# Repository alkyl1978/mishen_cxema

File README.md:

Схемы и прошивки основного блока и ракеток мишени

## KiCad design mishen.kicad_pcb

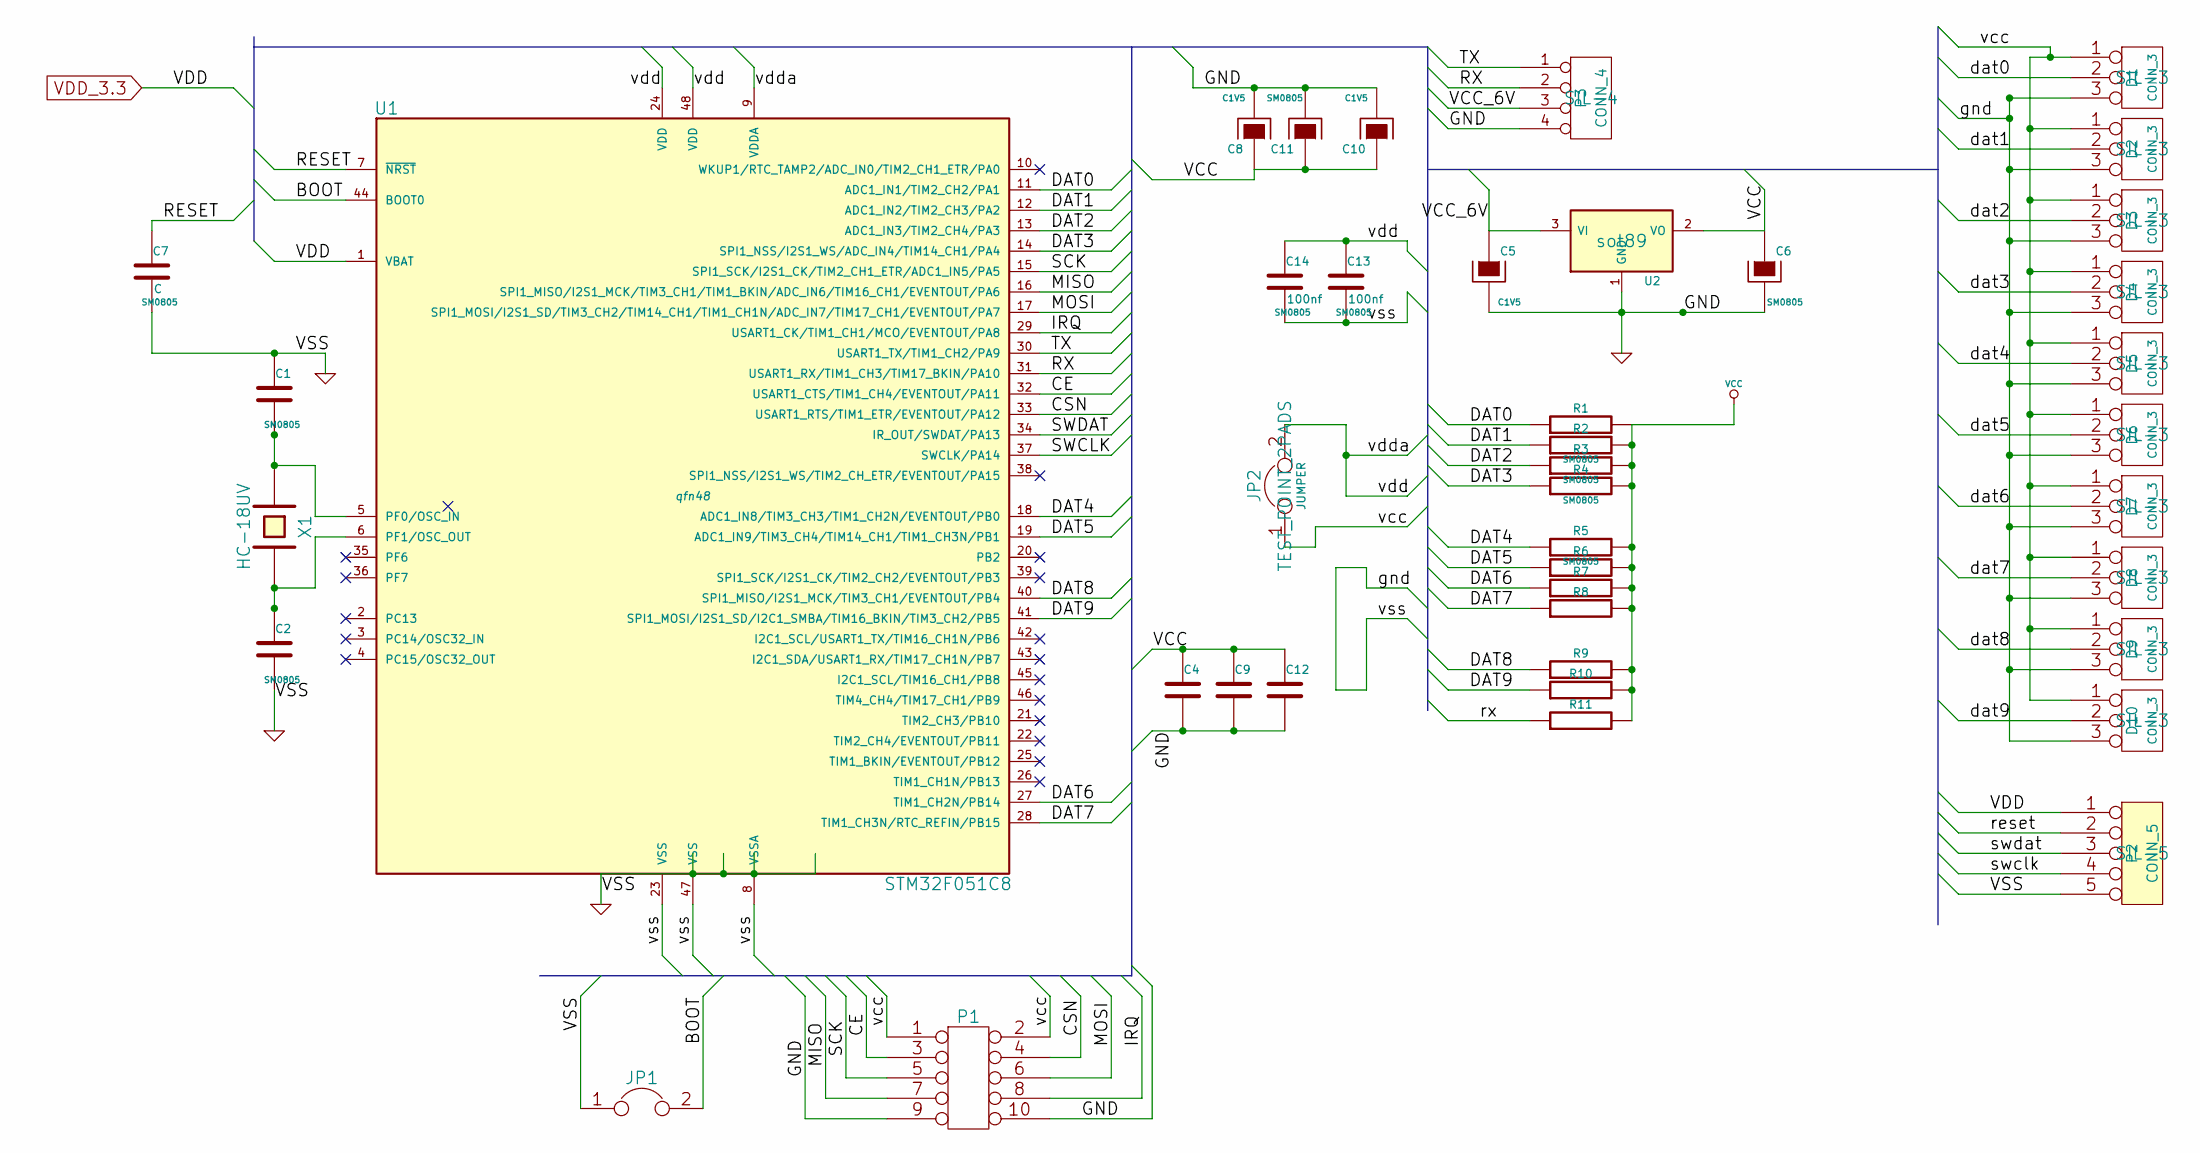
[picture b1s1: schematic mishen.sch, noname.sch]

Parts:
C1, C2: 10nf; SM0805
C4, C9, C12, C13, C14: 100nf; SM0805
C5: CAPAPOL; C1V5
C6: CAPAPOL; SM0805
C7: C; SM0805
C8, C10: 1uf; C1V5
C11: 1uf; SM0805
D1, D2, D3, D4, D5, D6, D7, D8, D9, D10: CONN_3; SIL-3
JP1, JP2: JUMPER; TEST_POINT_2PADS
P1: CONN_5X2; PIN_ARRAY_5x2
P2: CONN_5; SIL-5
P3: CONN_4; SIL-4
R1: 1KOM; SM0805
R2, R3, R4, R5, R6, R7, R8, R9, R10, R11: R; SM0805
U1: STM32F051С8; qfn48
U2: NCP1117ST33T3G; sot89
X1: 16MGZ; HC-18UV

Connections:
/BOOT: JP1.2, U1.44 (BOOT0)
/CE: P1.3, U1.32 (USART1_CTS/TIM1_CH4/EVENTOUT/PA11)
/CSN: P1.4, U1.33 (USART1_RTS/TIM1_ETR/EVENTOUT/PA12)
/DAT0: D1.2 (PM), R1.1, U1.11 (ADC1_IN1/TIM2_CH2/PA1)
/DAT1: D2.2 (PM), R2.1, U1.12 (ADC1_IN2/TIM2_CH3/PA2)
/DAT2: D3.2 (PM), R3.1, U1.13 (ADC1_IN3/TIM2_CH4/PA3)
/DAT3: D4.2 (PM), R4.1, U1.14 (SPI1_NSS/I2S1_WS/ADC_IN4/TIM14_CH1/PA4)
/DAT4: D5.2 (PM), R5.1, U1.18 (ADC1_IN8/TIM3_CH3/TIM1_CH2N/EVENTOUT/PB0)
/DAT5: D6.2 (PM), R6.1, U1.19 (ADC1_IN9/TIM3_CH4/TIM14_CH1/TIM1_CH3N/P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)
/DAT6: D7.2 (PM), R7.1, U1.27 (TIM1_CH2N/PB14)
/DAT7: D8.2 (PM), R8.1, U1.28 (TIM1_CH3N/RTC_REFIN/PB15)
/DAT8: D9.2 (PM), R9.1, U1.40 (SPI1_MISO/I2S1_MCK/TIM3_CH1/EVENTOUT/PB4)
/DAT9: D10.2 (PM), R10.1, U1.41 (SPI1_MOSI/I2S1_SD/I2C1_SMBA/TIM16_BKIN/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)
/IRQ: P1.8, U1.29 (USART1_CK/TIM1_CH1/MCO/EVENTOUT/PA8)
/MISO: P1.7, U1.16 (SPI1_MISO/I2S1_MCK/TIM3_CH1/TIM1_BKIN/A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)
/MOSI: P1.6, U1.17 (SPI1_MOSI/I2S1_SD/TIM3_CH2/TIM14_CH1/TI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)
/RESET: C7.1, P2.2, U1.7 (~NRST)
/RX: P3.2, R11.1, U1.31 (USART1_RX/TIM1_CH3/TIM17_BKIN/PA10)
/SCK: P1.5, U1.15 (SPI1_SCK/I2S1_CK/TIM2_CH1_ETR/ADC1_IN5/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)
/SWCLK: P2.4, U1.37 (SWCLK/PA14)
/SWDAT: P2.3, U1.34 (IR_OUT/SWDAT/PA13)
/TX: P3.1, U1.30 (USART1_TX/TIM1_CH2/PA9)
/VCC_6V: C5.1, P3.3, U2.3 (VI)
GND: C1.1, C2.2, C4.2, C5.2, C6.2, C7.2, C8.2, C9.2, C10.2, C11.2, C12.2, C13.2, C14.2, D1.3, D2.3, D3.3, D4.3, D5.3, D6.3, D7.3, D8.3, D9.3, D10.3, JP1.1, P1.9, P1.10, P2.5, P3.4, U1.8 (VSSA), U1.23 (VSS), U1.47 (VSS), U2.1 (GND)
unnamed: C2.1, U1.6 (PF1/OSC_OUT), X1.2
unnamed: C1.2, U1.5 (PF0/OSC_IN), X1.1
VCC: C4.1, C6.1, C8.1, C9.1, C10.1, C11.1, C12.1, D1.1, D2.1, D3.1, D4.1, D5.1, D6.1, D7.1, D8.1, D9.1, D10.1, JP2.1, P1.1, P1.2, R1.2, R2.2, R3.2, R4.2, R5.2, R6.2, R7.2, R8.2, R9.2, R10.2, R11.2, U2.2 (VO)
VDD_3.3: C13.1, C14.1, JP2.2, P2.1, U1.1 (VBAT), U1.9 (VDDA), U1.24 (VDD), U1.48 (VDD)

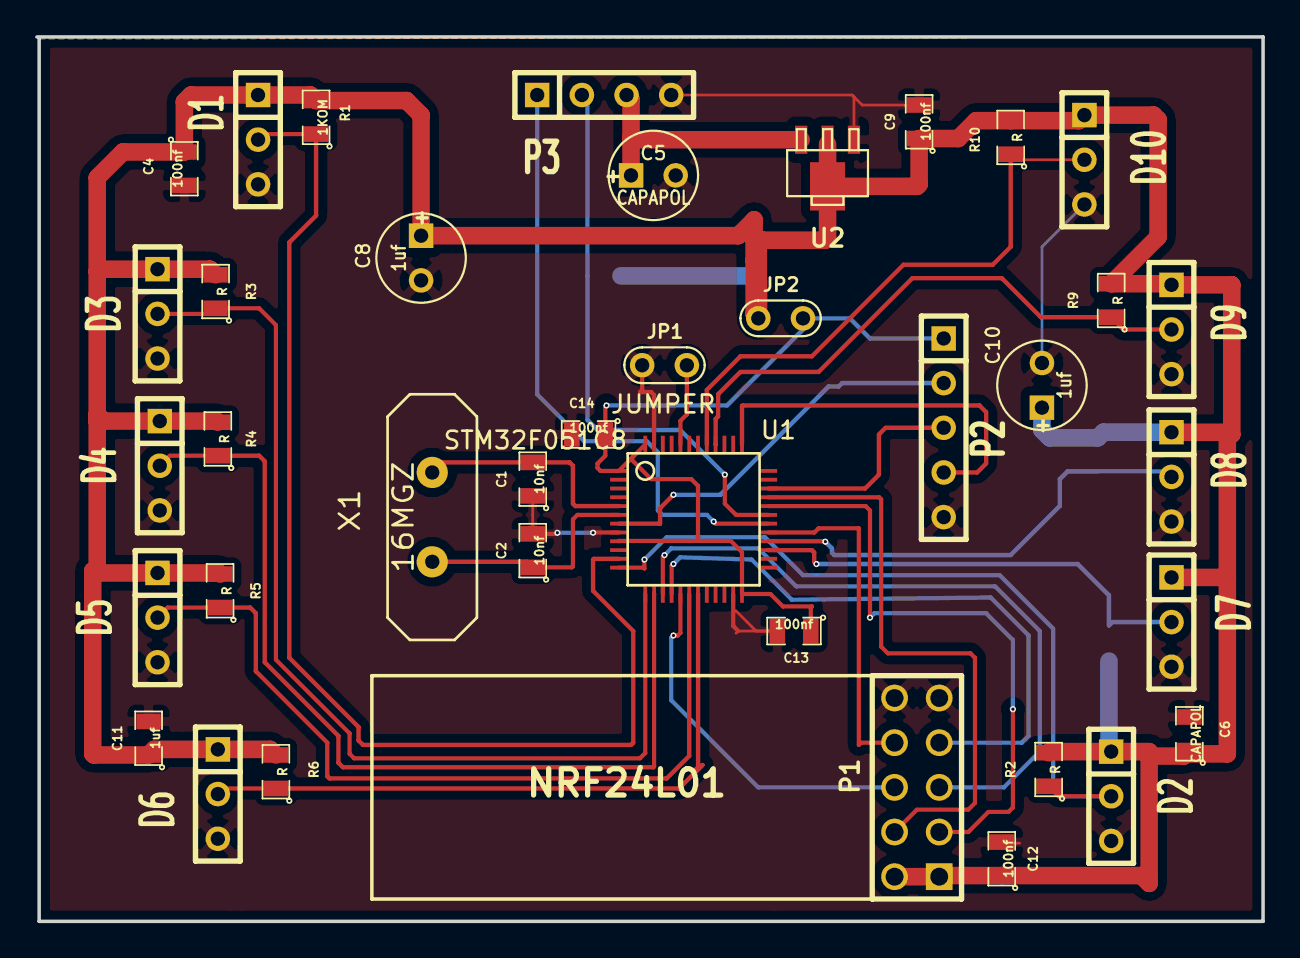
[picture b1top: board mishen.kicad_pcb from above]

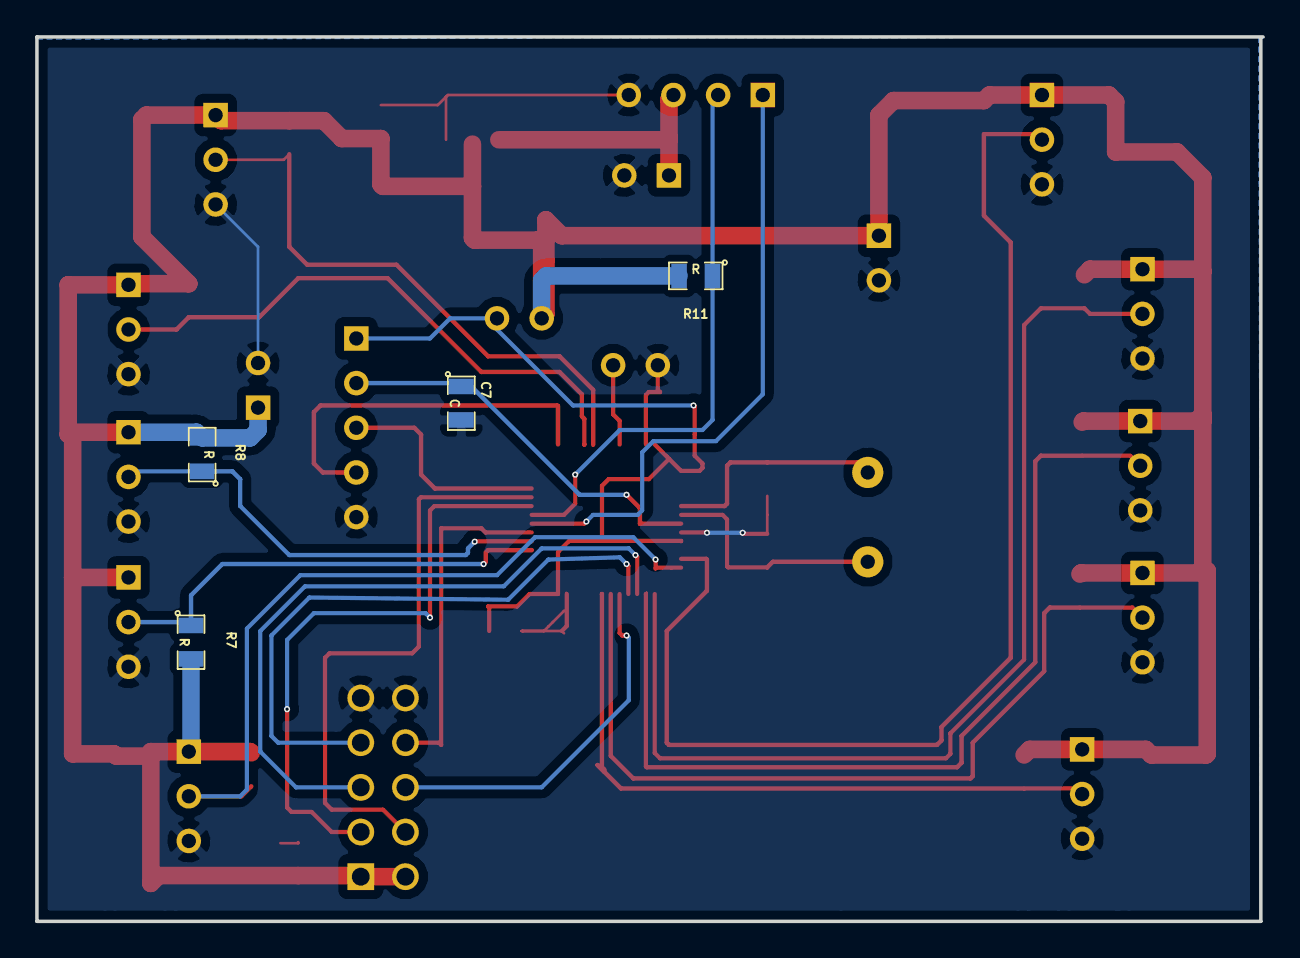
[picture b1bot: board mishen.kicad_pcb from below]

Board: 2 copper layers, 69.7 x 50.3 mm, 42 parts (4 on the bottom side), 28 nets.

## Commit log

2015-11-22 first init
2016-08-26 разложил по папкам
2016-08-26 Добавлены файлы исходное по мишени и прошивки и схемы ракеток и основного блока и документация
